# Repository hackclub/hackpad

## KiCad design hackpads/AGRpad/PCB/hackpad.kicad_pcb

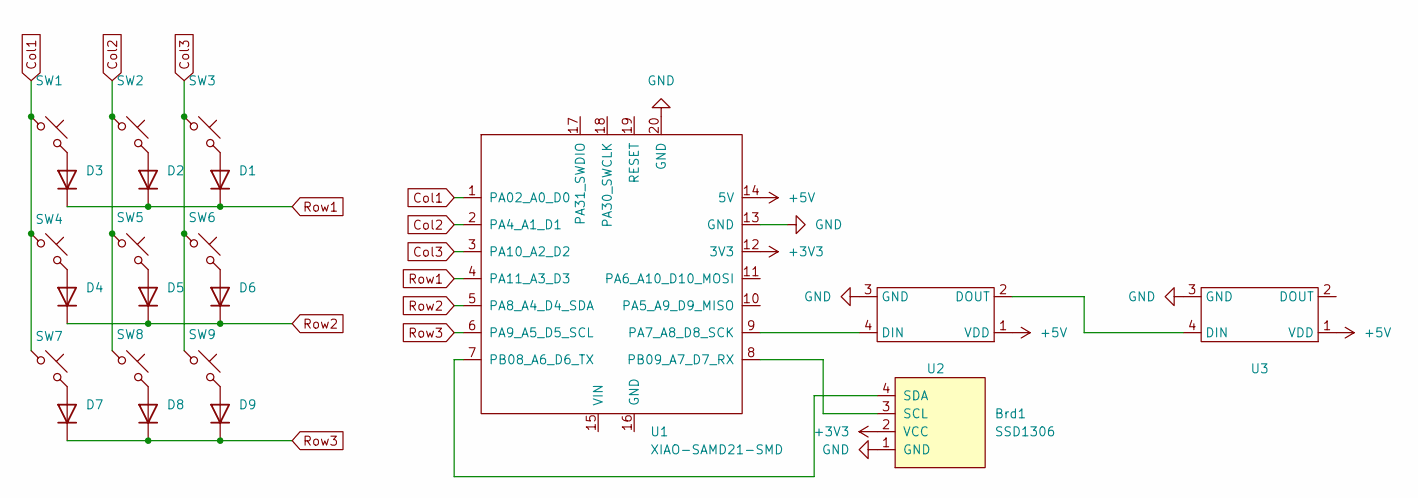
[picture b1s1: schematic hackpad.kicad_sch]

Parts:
Brd1: SSD1306; Display_128x64_096_I2C
D1, D2, D3, D4, D5, D6, D7, D8, D9: 1N4148WT; D_DO-34_SOD68_P7.62mm_Horizontal
SW1, SW2, SW3, SW4, SW5, SW6, SW7, SW8, SW9: SW_Push_45deg; SW_Cherry_MX_1.00u_PCB
U1: XIAO-SAMD21-SMD; XIAO-RP2040-DIP
U2, U3: LED_SK6812MINI_PLCC4_3.5x3.5mm_P1.75mm

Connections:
+3V3: Brd1.2 (VCC), U1.12 (3V3)
+5V: U1.14 (5V), U2.1 (VDD), U3.1 (VDD)
Col1: SW1.1, SW4.1, SW7.1, U1.1 (PA02_A0_D0)
Col2: SW2.1, SW5.1, SW8.1, U1.2 (PA4_A1_D1)
Col3: SW3.1, SW6.1, SW9.1, U1.3 (PA10_A2_D2)
GND: Brd1.1 (GND), U1.13 (GND), U1.20 (GND), U2.3 (GND), U3.3 (GND)
unnamed: Brd1.3 (SCL), U1.8 (PB09_A7_D7_RX)
unnamed: Brd1.4 (SDA), U1.7 (PB08_A6_D6_TX)
unnamed: D1.2 (A), SW3.2
unnamed: D2.2 (A), SW2.2
unnamed: D3.2 (A), SW1.2
unnamed: D4.2 (A), SW4.2
unnamed: D5.2 (A), SW5.2
unnamed: D6.2 (A), SW6.2
unnamed: D7.2 (A), SW7.2
unnamed: D8.2 (A), SW8.2
unnamed: D9.2 (A), SW9.2
unnamed: U1.9 (PA7_A8_D8_SCK), U2.4 (DIN)
unnamed: U2.2 (DOUT), U3.4 (DIN)
Row1: D1.1 (K), D2.1 (K), D3.1 (K), U1.4 (PA11_A3_D3)
Row2: D4.1 (K), D5.1 (K), D6.1 (K), U1.5 (PA8_A4_D4_SDA)
Row3: D7.1 (K), D8.1 (K), D9.1 (K), U1.6 (PA9_A5_D5_SCL)

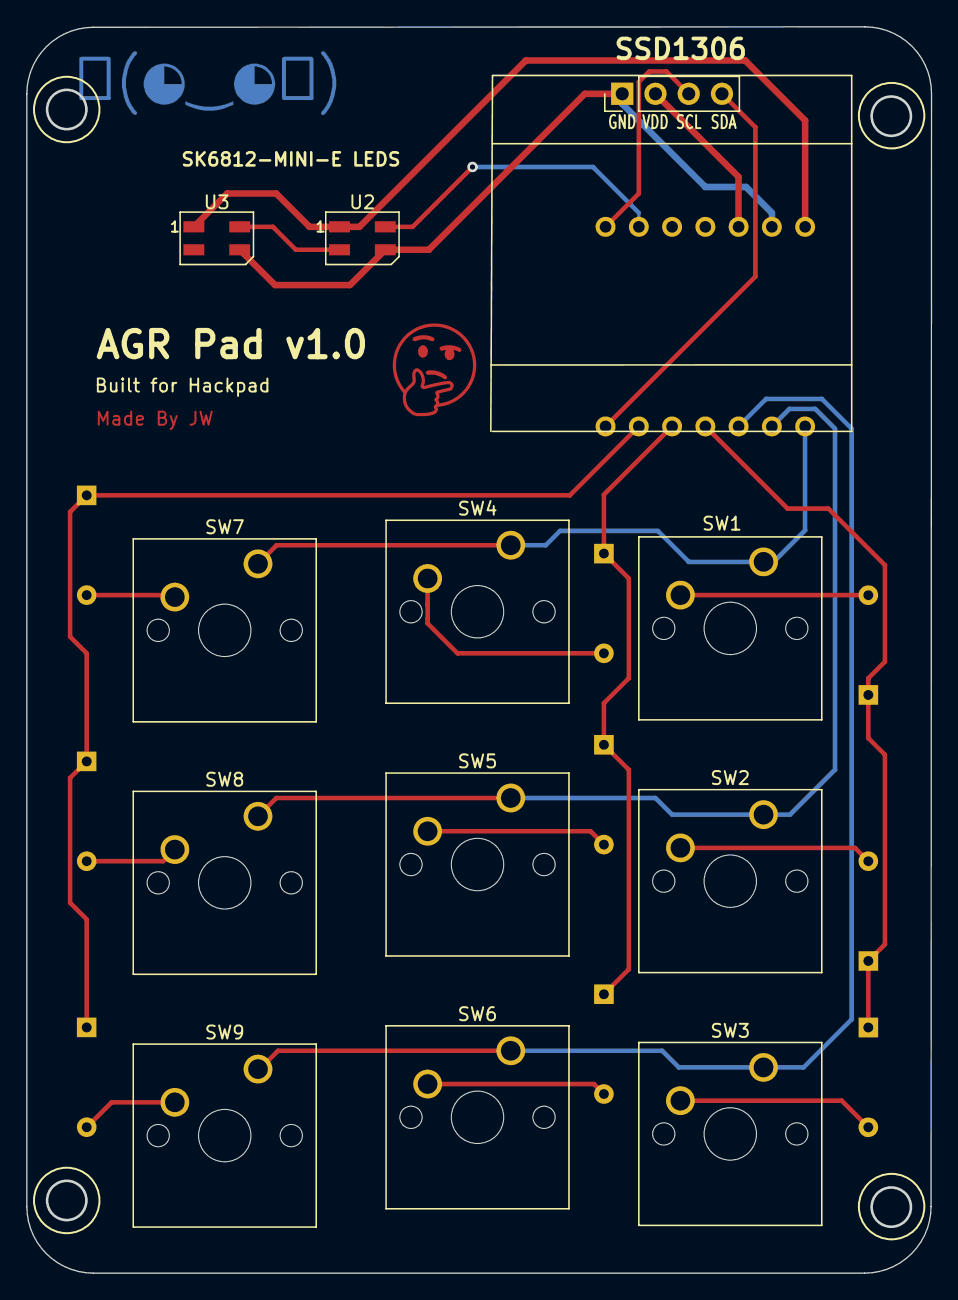
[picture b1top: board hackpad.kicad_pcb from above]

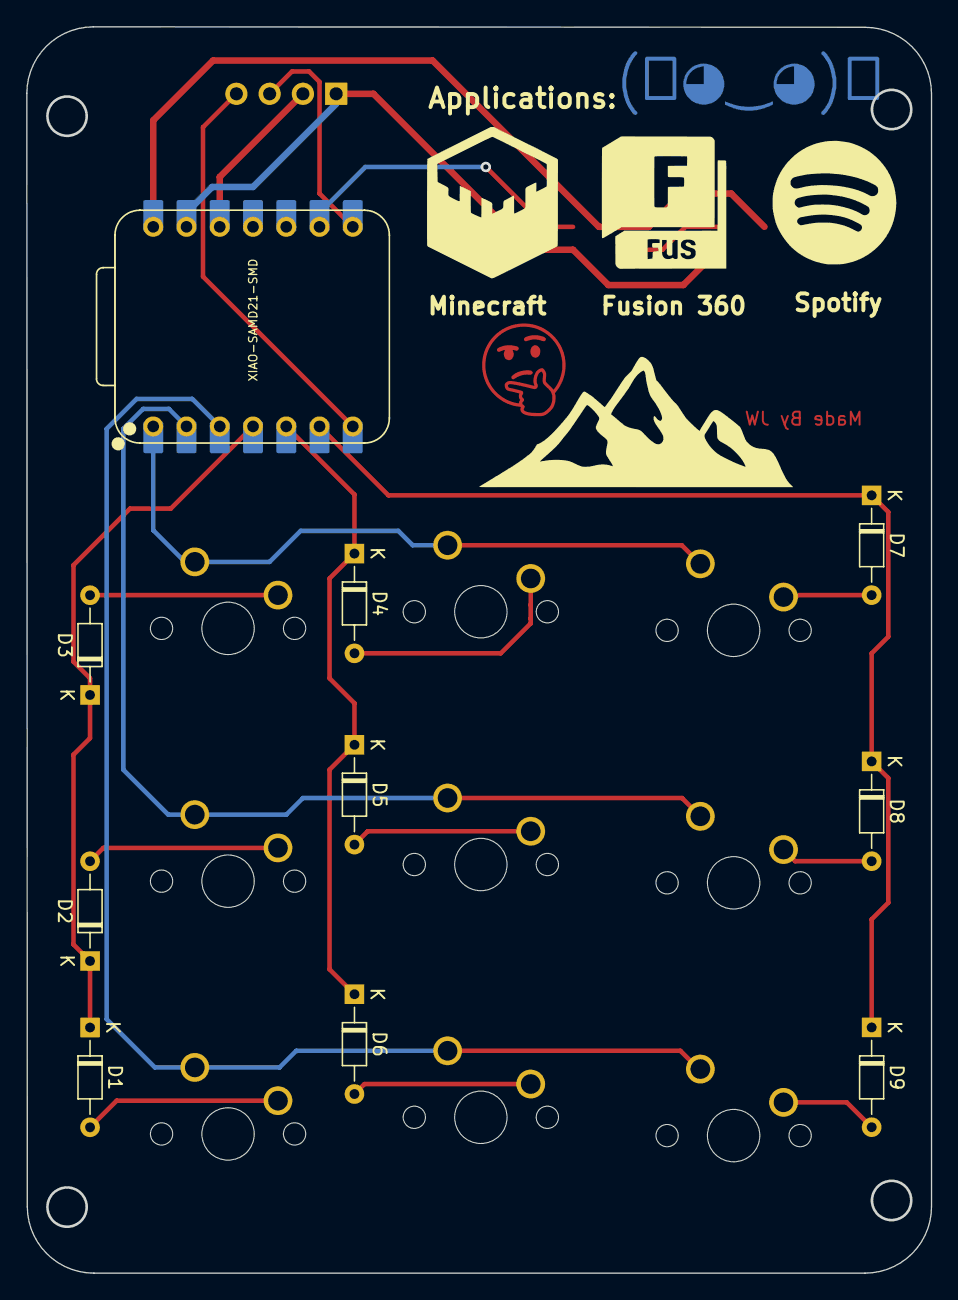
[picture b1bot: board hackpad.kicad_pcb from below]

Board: 2 copper layers, 69.1 x 95.2 mm, 22 parts (10 on the bottom side), 22 nets.

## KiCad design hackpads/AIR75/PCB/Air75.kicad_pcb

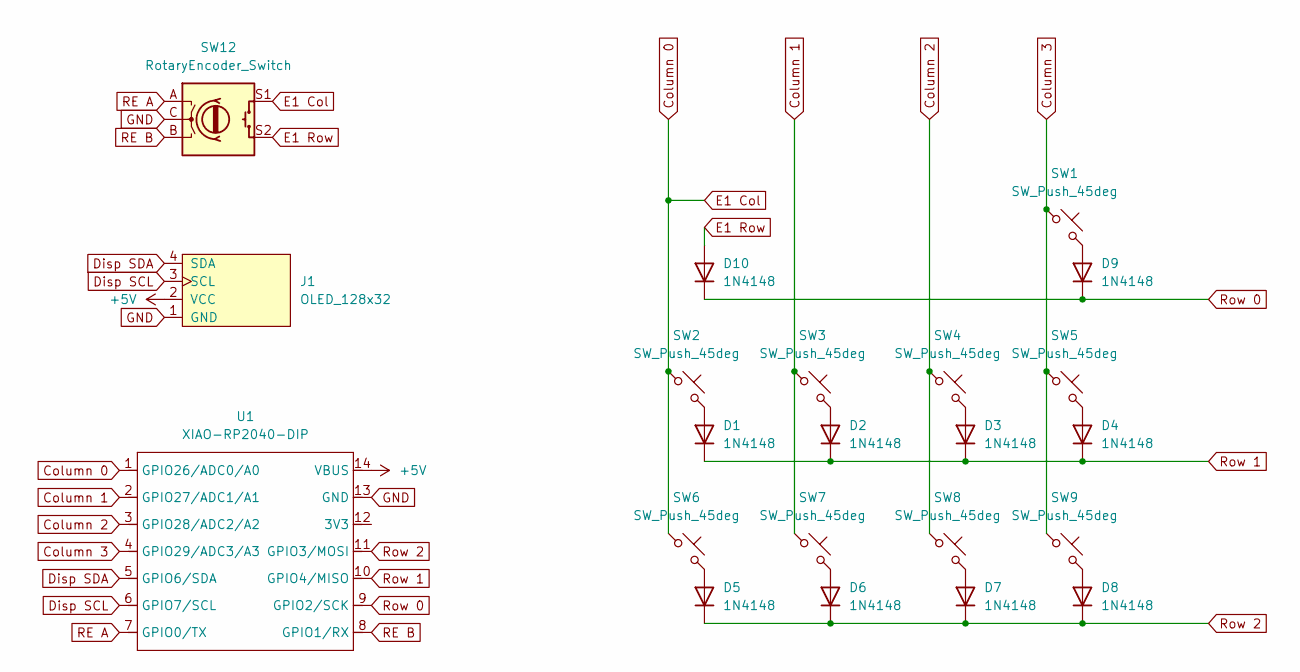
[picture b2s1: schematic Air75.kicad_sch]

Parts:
D1, D2, D3, D4, D5, D6, D7, D8, D9, D10: 1N4148; D_DO-35_SOD27_P7.62mm_Horizontal
J1: OLED_128x32
SW1, SW2, SW3, SW4, SW5, SW6, SW7, SW8, SW9: SW_Push_45deg; MX_PCB_1.00u
SW12: RotaryEncoder_Switch; Encoder_EC11_MX_Combo
U1: XIAO-RP2040-DIP

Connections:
+5V: J1.2 (VCC), U1.14 (VBUS)
Column 0: SW2.1, SW6.1, SW12.S1, U1.1 (GPIO26/ADC0/A0)
Column 1: SW3.1, SW7.1, U1.2 (GPIO27/ADC1/A1)
Column 2: SW4.1, SW8.1, U1.3 (GPIO28/ADC2/A2)
Column 3: SW1.1, SW5.1, SW9.1, U1.4 (GPIO29/ADC3/A3)
Disp SCL: J1.3 (SCL), U1.6 (GPIO7/SCL)
Disp SDA: J1.4 (SDA), U1.5 (GPIO6/SDA)
E1 Row: D10.2 (A), SW12.S2
GND: J1.1 (GND), SW12.C, U1.13 (GND)
unnamed: D1.2 (A), SW2.2
unnamed: D2.2 (A), SW3.2
unnamed: D3.2 (A), SW4.2
unnamed: D4.2 (A), SW5.2
unnamed: D5.2 (A), SW6.2
unnamed: D6.2 (A), SW7.2
unnamed: D7.2 (A), SW8.2
unnamed: D8.2 (A), SW9.2
unnamed: D9.2 (A), SW1.2
RE A: SW12.A, U1.7 (GPIO0/TX)
RE B: SW12.B, U1.8 (GPIO1/RX)
Row 0: D9.1 (K), D10.1 (K), U1.9 (GPIO2/SCK)
Row 1: D1.1 (K), D2.1 (K), D3.1 (K), D4.1 (K), U1.10 (GPIO4/MISO)
Row 2: D5.1 (K), D6.1 (K), D7.1 (K), D8.1 (K), U1.11 (GPIO3/MOSI)

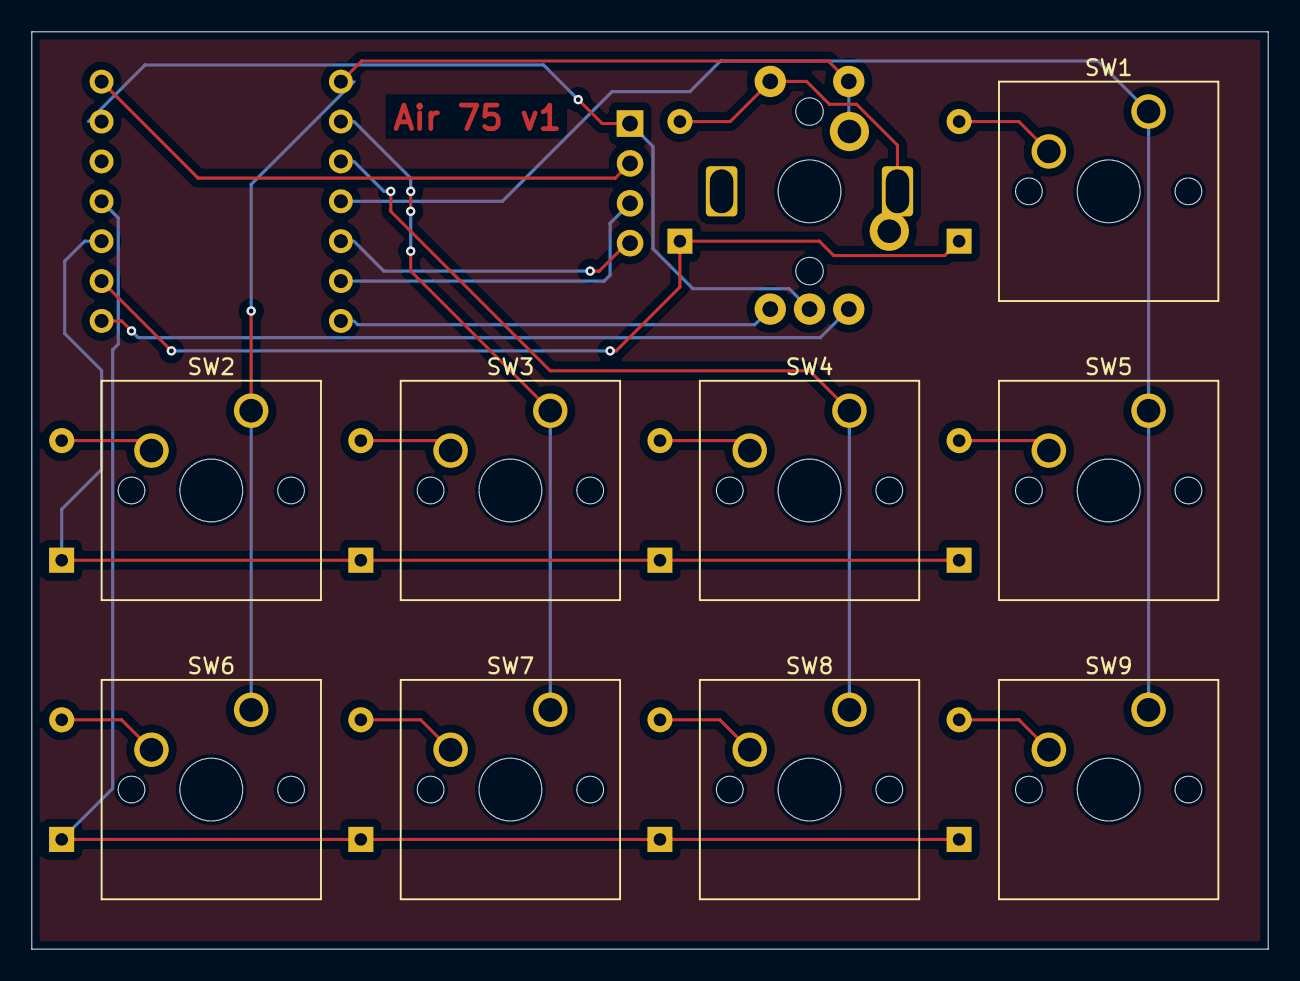
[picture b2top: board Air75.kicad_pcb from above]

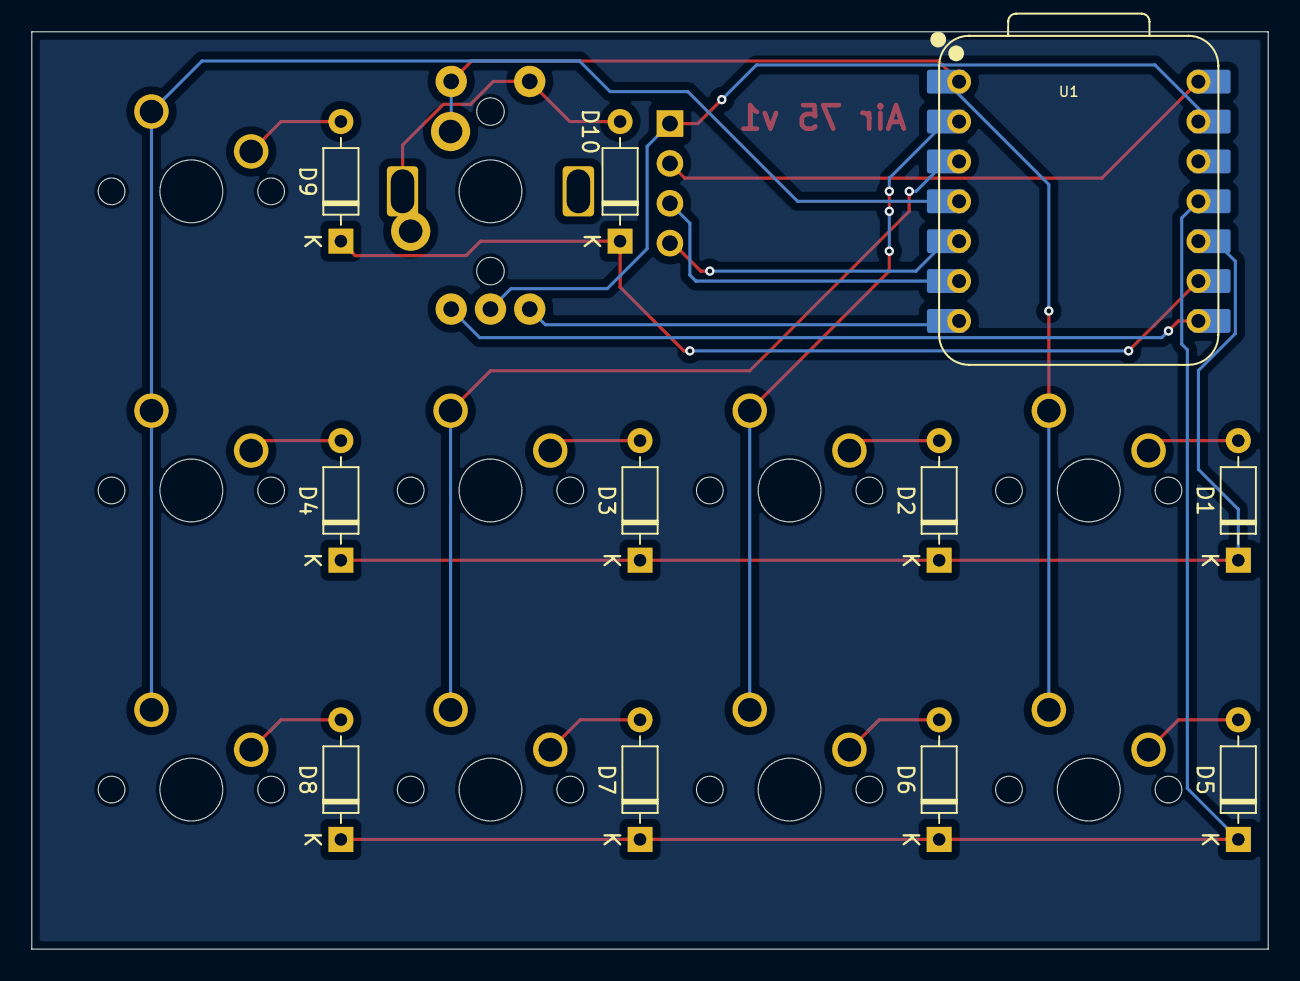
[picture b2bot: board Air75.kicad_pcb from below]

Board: 2 copper layers, 78.7 x 58.4 mm, 22 parts (11 on the bottom side), 23 nets.

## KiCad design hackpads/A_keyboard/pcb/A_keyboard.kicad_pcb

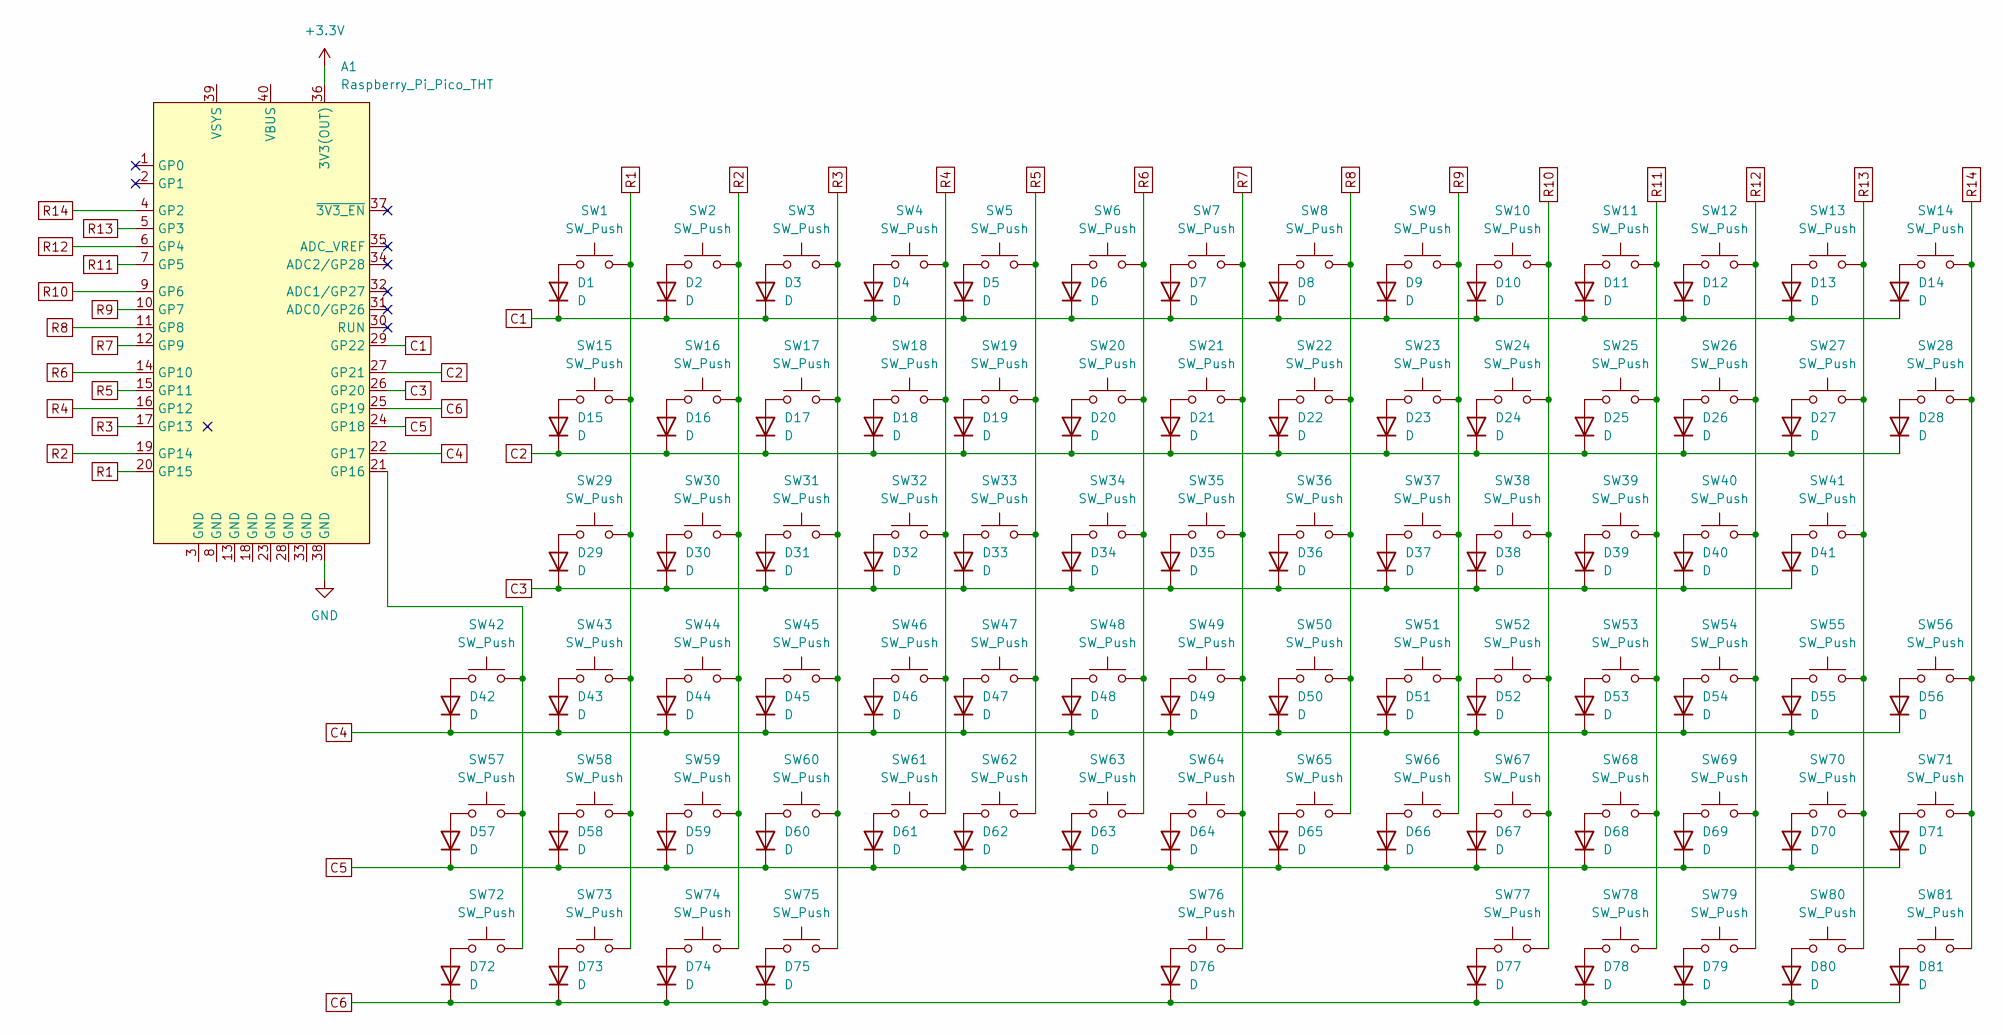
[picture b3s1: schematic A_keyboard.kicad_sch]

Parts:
A1: Raspberry_Pi_Pico_THT; RaspberryPi_Pico_Common_THT
D1, D2, D3, D4, D5, D6, D7, D8, D9, D10, D11, D12, D13, D14, D15, D16, D17, D18, D19, D20, D21, D22, D23, D24, D25, D26, D27, D28, D29, D30, D31, D32, D33, D34, D35, D36, D37, D38, D39, D40, D41, D42, D43, D44, D45, D46, D47, D48, D49, D50, D51, D52, D53, D54, D55, D56, D57, D58, D59, D60, D61, D62, D63, D64, D65, D66, D67, D68, D69, D70, D71, D72, D73, D74, D75, D76, D77, D78, D79, D80, D81: D; D_DO-35_SOD27_P7.62mm_Horizontal
SW1, SW2, SW3, SW4, SW5, SW6, SW7, SW8, SW9, SW10, SW11, SW12, SW13, SW14, SW15, SW16, SW17, SW18, SW19, SW20, SW21, SW22, SW23, SW24, SW25, SW26, SW27, SW30, SW31, SW32, SW33, SW34, SW35, SW36, SW37, SW38, SW39, SW40, SW41, SW42, SW44, SW45, SW46, SW47, SW48, SW49, SW50, SW51, SW52, SW53, SW54, SW55, SW56, SW57, SW59, SW60, SW61, SW62, SW63, SW64, SW65, SW66, SW67, SW68, SW69, SW70, SW71, SW72, SW77, SW78, SW79, SW80, SW81: SW_Push; MX-Hotswap-1U
SW28, SW58: SW_Push; MX-Hotswap-2U
SW29: SW_Push; MX-Hotswap-1.5U
SW43: SW_Push; MX-Hotswap-1.75U
SW73, SW74, SW75: SW_Push; MX-Hotswap-1.25U
SW76: SW_Push; MX-Hotswap-6.25U

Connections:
+3.3V: A1.36 (3V3(OUT))
C1: A1.29 (GP22), D1.1 (K), D2.1 (K), D3.1 (K), D4.1 (K), D5.1 (K), D6.1 (K), D7.1 (K), D8.1 (K), D9.1 (K), D10.1 (K), D11.1 (K), D12.1 (K), D13.1 (K), D14.1 (K)
C2: A1.27 (GP21), D15.1 (K), D16.1 (K), D17.1 (K), D18.1 (K), D19.1 (K), D20.1 (K), D21.1 (K), D22.1 (K), D23.1 (K), D24.1 (K), D25.1 (K), D26.1 (K), D27.1 (K), D28.1 (K)
C3: A1.26 (GP20), D29.1 (K), D30.1 (K), D31.1 (K), D32.1 (K), D33.1 (K), D34.1 (K), D35.1 (K), D36.1 (K), D37.1 (K), D38.1 (K), D39.1 (K), D40.1 (K), D41.1 (K)
C4: A1.22 (GP17), D42.1 (K), D43.1 (K), D44.1 (K), D45.1 (K), D46.1 (K), D47.1 (K), D48.1 (K), D49.1 (K), D50.1 (K), D51.1 (K), D52.1 (K), D53.1 (K), D54.1 (K), D55.1 (K), D56.1 (K)
C5: A1.24 (GP18), D57.1 (K), D58.1 (K), D59.1 (K), D60.1 (K), D61.1 (K), D62.1 (K), D63.1 (K), D64.1 (K), D65.1 (K), D66.1 (K), D67.1 (K), D68.1 (K), D69.1 (K), D70.1 (K), D71.1 (K)
C6: A1.25 (GP19), D72.1 (K), D73.1 (K), D74.1 (K), D75.1 (K), D76.1 (K), D77.1 (K), D78.1 (K), D79.1 (K), D80.1 (K), D81.1 (K)
GND: A1.38 (GND)
unnamed: A1.21 (GP16), SW42.1, SW57.1, SW72.1
unnamed: D1.2 (A), SW1.2
unnamed: D2.2 (A), SW2.2
unnamed: D3.2 (A), SW3.2
unnamed: D4.2 (A), SW4.2
unnamed: D5.2 (A), SW5.2
unnamed: D6.2 (A), SW6.2
unnamed: D7.2 (A), SW7.2
unnamed: D8.2 (A), SW8.2
unnamed: D9.2 (A), SW9.2
unnamed: D10.2 (A), SW10.2
unnamed: D11.2 (A), SW11.2
unnamed: D12.2 (A), SW12.2
unnamed: D13.2 (A), SW13.2
unnamed: D14.2 (A), SW14.2
unnamed: D15.2 (A), SW15.2
unnamed: D16.2 (A), SW16.2
unnamed: D17.2 (A), SW17.2
unnamed: D18.2 (A), SW18.2
unnamed: D19.2 (A), SW19.2
unnamed: D20.2 (A), SW20.2
unnamed: D21.2 (A), SW21.2
unnamed: D22.2 (A), SW22.2
unnamed: D23.2 (A), SW23.2
unnamed: D24.2 (A), SW24.2
unnamed: D25.2 (A), SW25.2
unnamed: D26.2 (A), SW26.2
unnamed: D27.2 (A), SW27.2
unnamed: D28.2 (A), SW28.2
unnamed: D29.2 (A), SW29.2
unnamed: D30.2 (A), SW30.2
unnamed: D31.2 (A), SW31.2
unnamed: D32.2 (A), SW32.2
unnamed: D33.2 (A), SW33.2
unnamed: D34.2 (A), SW34.2
unnamed: D35.2 (A), SW35.2
unnamed: D36.2 (A), SW36.2
unnamed: D37.2 (A), SW37.2
unnamed: D38.2 (A), SW38.2
unnamed: D39.2 (A), SW39.2
unnamed: D40.2 (A), SW40.2
unnamed: D41.2 (A), SW41.2
unnamed: D42.2 (A), SW42.2
unnamed: D43.2 (A), SW43.2
unnamed: D44.2 (A), SW44.2
unnamed: D45.2 (A), SW45.2
unnamed: D46.2 (A), SW46.2
unnamed: D47.2 (A), SW47.2
unnamed: D48.2 (A), SW48.2
unnamed: D49.2 (A), SW49.2
unnamed: D50.2 (A), SW50.2
unnamed: D51.2 (A), SW51.2
unnamed: D52.2 (A), SW52.2
unnamed: D53.2 (A), SW53.2
unnamed: D54.2 (A), SW54.2
unnamed: D55.2 (A), SW55.2
unnamed: D56.2 (A), SW56.2
unnamed: D57.2 (A), SW57.2
unnamed: D58.2 (A), SW58.2
unnamed: D59.2 (A), SW59.2
unnamed: D60.2 (A), SW60.2
unnamed: D61.2 (A), SW61.2
unnamed: D62.2 (A), SW62.2
unnamed: D63.2 (A), SW63.2
unnamed: D64.2 (A), SW64.2
unnamed: D65.2 (A), SW65.2
unnamed: D66.2 (A), SW66.2
unnamed: D67.2 (A), SW67.2
unnamed: D68.2 (A), SW68.2
unnamed: D69.2 (A), SW69.2
unnamed: D70.2 (A), SW70.2
unnamed: D71.2 (A), SW71.2
unnamed: D72.2 (A), SW72.2
unnamed: D73.2 (A), SW73.2
unnamed: D74.2 (A), SW74.2
unnamed: D75.2 (A), SW75.2
unnamed: D76.2 (A), SW76.2
unnamed: D77.2 (A), SW77.2
unnamed: D78.2 (A), SW78.2
unnamed: D79.2 (A), SW79.2
unnamed: D80.2 (A), SW80.2
unnamed: D81.2 (A), SW81.2
R1: A1.20 (GP15), SW1.1, SW15.1, SW29.1, SW43.1, SW58.1, SW73.1
R2: A1.19 (GP14), SW2.1, SW16.1, SW30.1, SW44.1, SW59.1, SW74.1
R3: A1.17 (GP13), SW3.1, SW17.1, SW31.1, SW45.1, SW60.1, SW75.1
R4: A1.16 (GP12), SW4.1, SW18.1, SW32.1, SW46.1, SW61.1
R5: A1.15 (GP11), SW5.1, SW19.1, SW33.1, SW47.1, SW62.1
R6: A1.14 (GP10), SW6.1, SW20.1, SW34.1, SW48.1, SW63.1
R7: A1.12 (GP9), SW7.1, SW21.1, SW35.1, SW49.1, SW64.1, SW76.1
R8: A1.11 (GP8), SW8.1, SW22.1, SW36.1, SW50.1, SW65.1
R9: A1.10 (GP7), SW9.1, SW23.1, SW37.1, SW51.1, SW66.1
R10: A1.9 (GP6), SW10.1, SW24.1, SW38.1, SW52.1, SW67.1, SW77.1
R11: A1.7 (GP5), SW11.1, SW25.1, SW39.1, SW53.1, SW68.1, SW78.1
R12: A1.6 (GP4), SW12.1, SW26.1, SW40.1, SW54.1, SW69.1, SW79.1
R13: A1.5 (GP3), SW13.1, SW27.1, SW41.1, SW55.1, SW70.1, SW80.1
R14: A1.4 (GP2), SW14.1, SW28.1, SW56.1, SW71.1, SW81.1

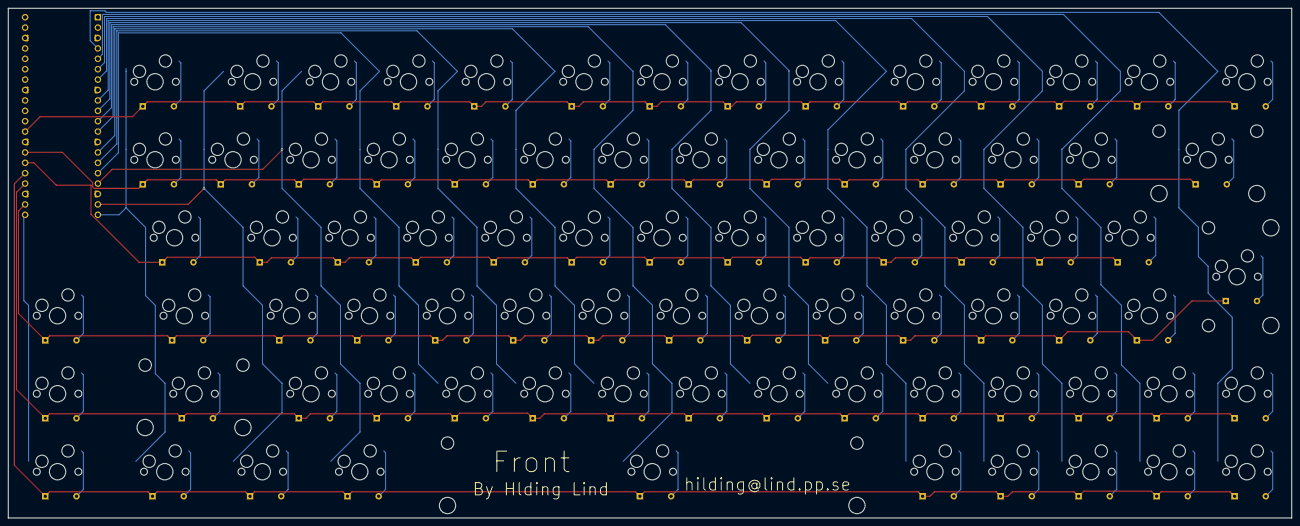
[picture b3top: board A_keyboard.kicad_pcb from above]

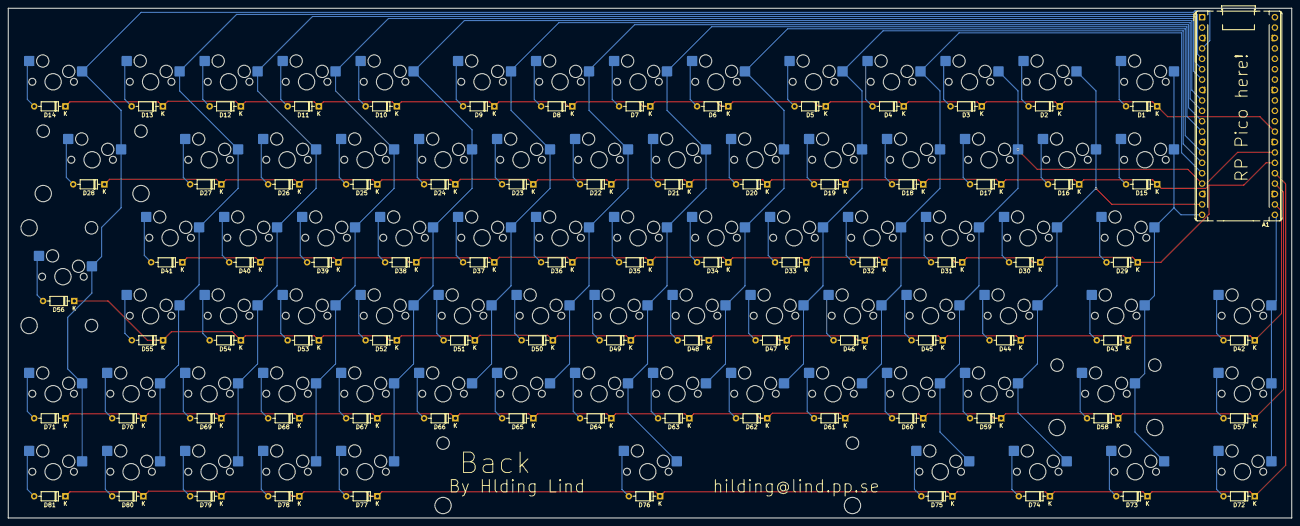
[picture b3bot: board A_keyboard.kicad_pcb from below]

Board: 2 copper layers, 313.5 x 124.5 mm, 163 parts (163 on the bottom side), 102 nets.

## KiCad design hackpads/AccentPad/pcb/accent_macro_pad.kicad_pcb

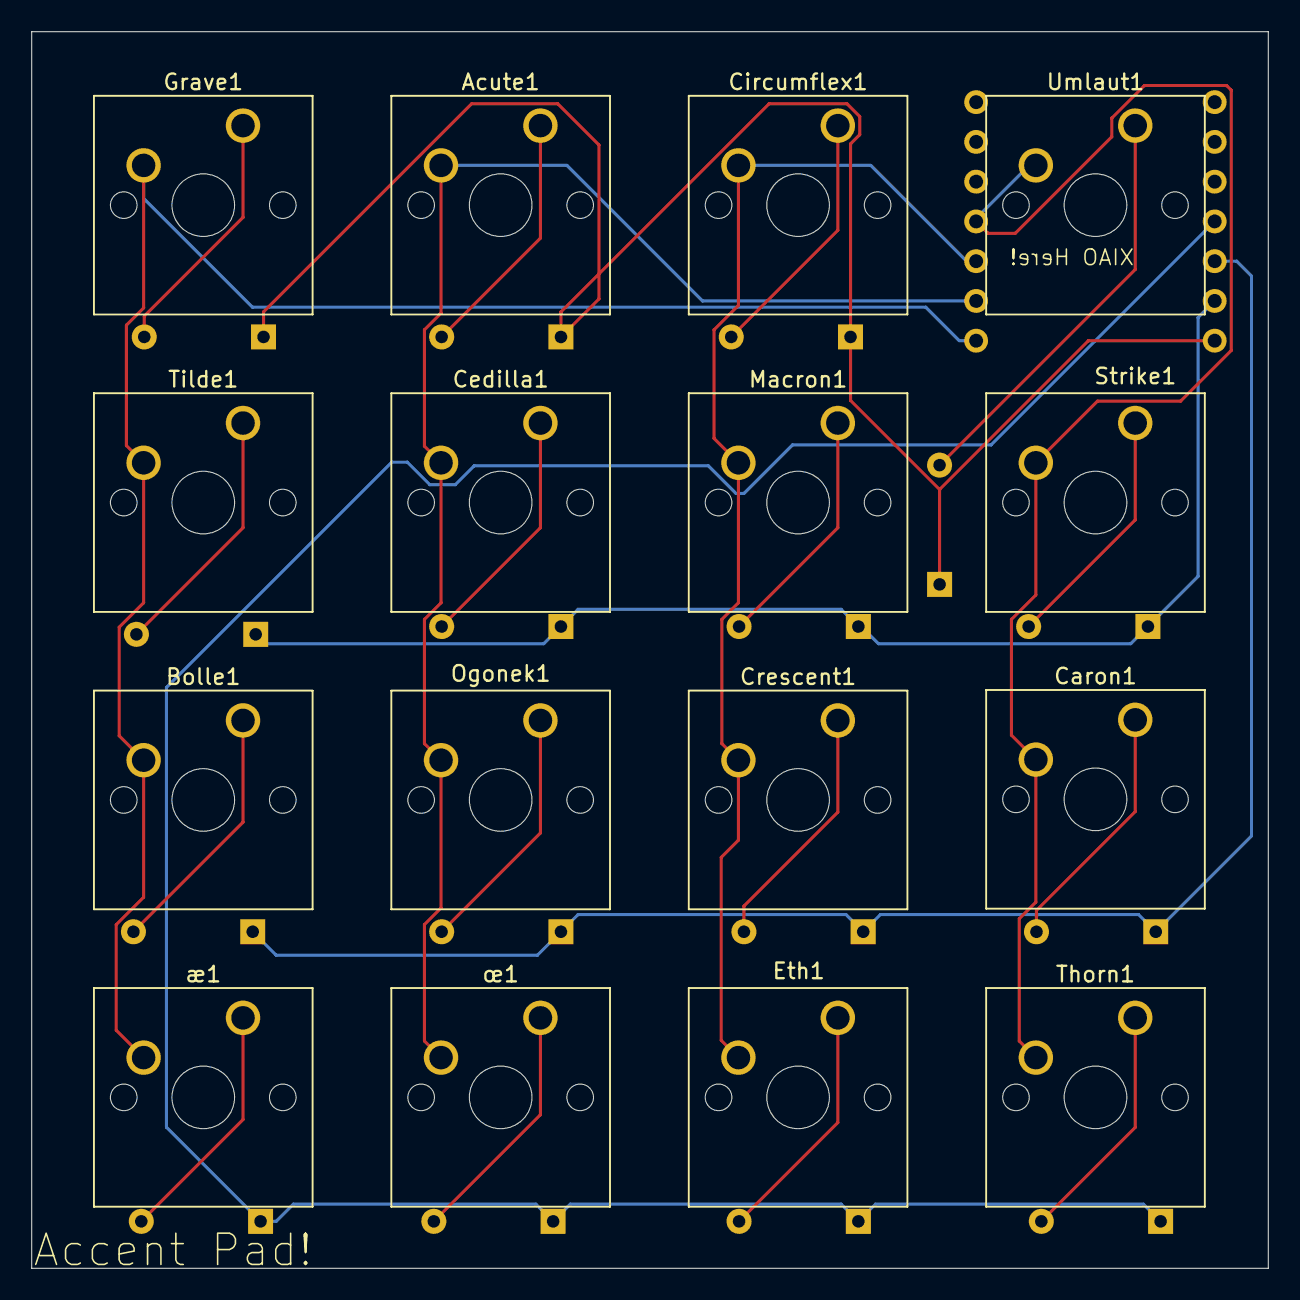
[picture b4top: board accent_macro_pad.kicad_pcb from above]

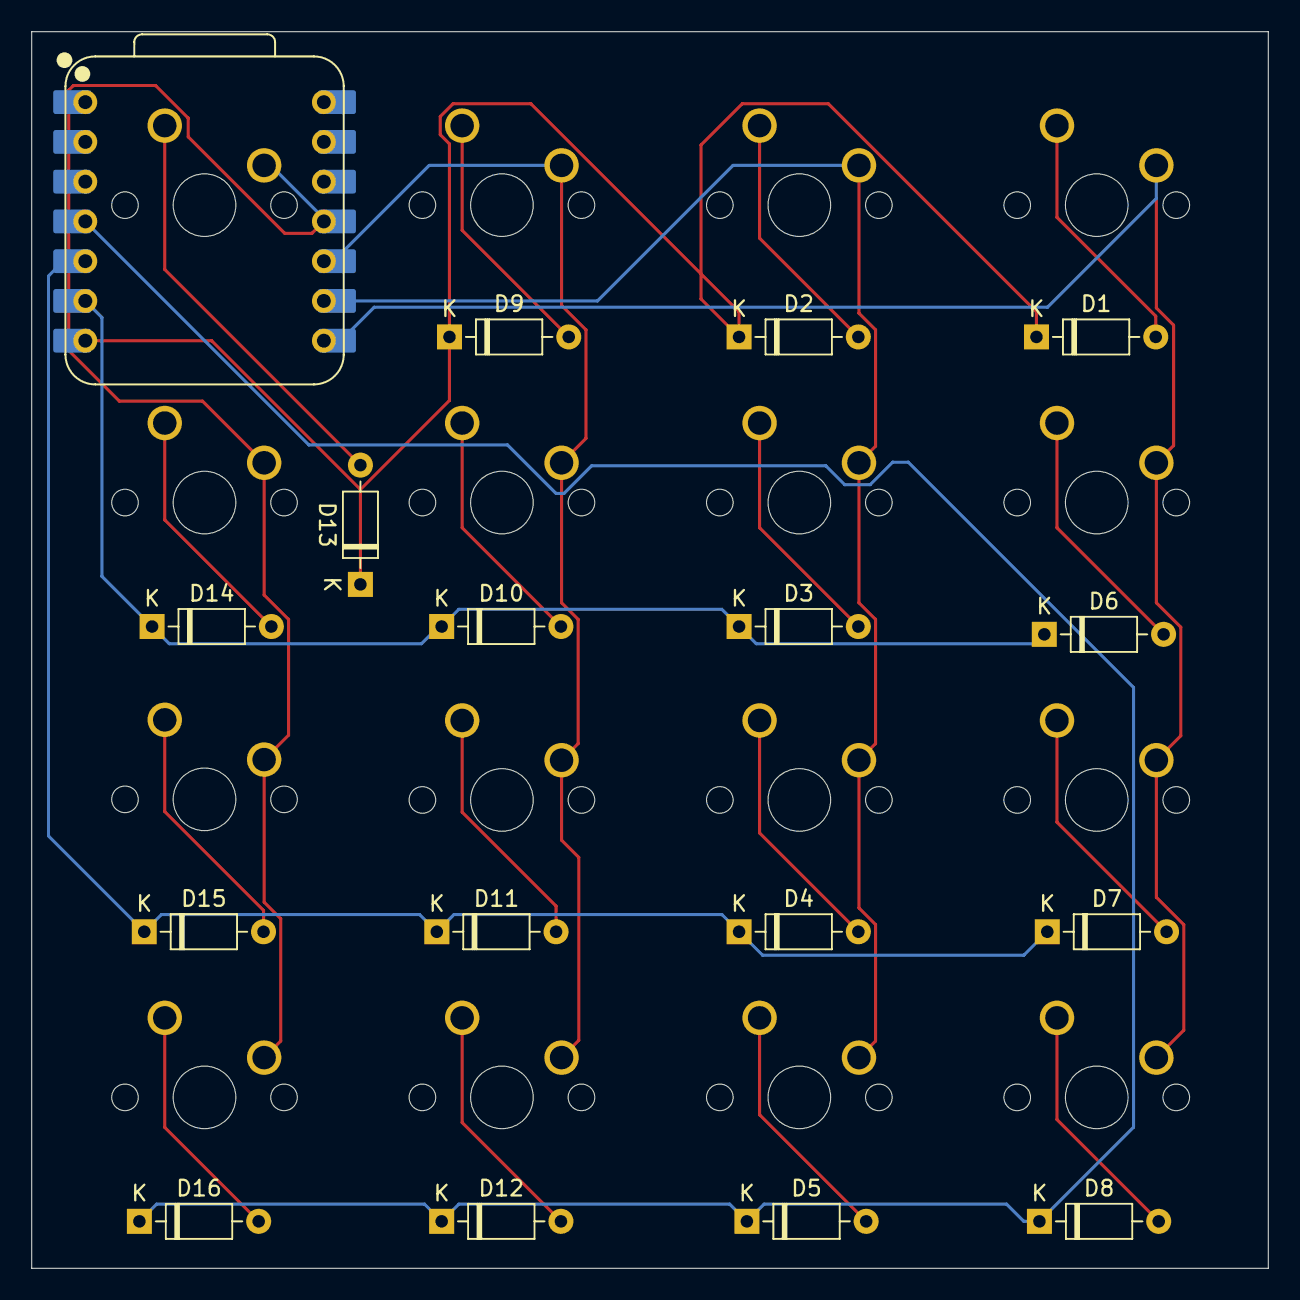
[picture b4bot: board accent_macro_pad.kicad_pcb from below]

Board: 2 copper layers, 79.0 x 79.0 mm, 33 parts (17 on the bottom side), 24 nets.

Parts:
Acute1: SW_Push; SW_Cherry_MX_1.00u_PCB
Bolle1: SW_Push; SW_Cherry_MX_1.00u_PCB
Caron1: SW_Push; SW_Cherry_MX_1.00u_PCB
Cedilla1: SW_Push; SW_Cherry_MX_1.00u_PCB
Circumflex1: SW_Push; SW_Cherry_MX_1.00u_PCB
Crescent1: SW_Push; SW_Cherry_MX_1.00u_PCB
D1, D2, D3, D4, D5, D6, D7, D8, D9, D10, D11, D12, D13, D14, D15, D16: 1N4148; D_DO-35_SOD27_P7.62mm_Horizontal
Eth1: SW_Push; SW_Cherry_MX_1.00u_PCB
Grave1: SW_Push; SW_Cherry_MX_1.00u_PCB
Macron1: SW_Push; SW_Cherry_MX_1.00u_PCB
Ogonek1: SW_Push; SW_Cherry_MX_1.00u_PCB
Strike1: SW_Push; SW_Cherry_MX_1.00u_PCB
Thorn1: SW_Push; SW_Cherry_MX_1.00u_PCB
Tilde1: SW_Push; SW_Cherry_MX_1.00u_PCB
U1: XIAO-RP2040-SMD; XIAO-RP2040-DIP
Umlaut1: SW_Push; SW_Cherry_MX_1.00u_PCB
æ1: SW_Push; SW_Cherry_MX_1.00u_PCB
œ1: SW_Push; SW_Cherry_MX_1.00u_PCB

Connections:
unnamed: D1.2 (A), Grave1.1
unnamed: D1.1 (K), D2.1 (K), D9.1 (K), D13.1 (K), U1.7 (GPIO0_D6_TX)
unnamed: Acute1.1, D2.2 (A)
unnamed: Cedilla1.1, D3.2 (A)
unnamed: D4.2 (A), Ogonek1.1
unnamed: D5.2 (A), œ1.1
unnamed: D6.2 (A), Tilde1.1
unnamed: Bolle1.1, D7.2 (A)
unnamed: D8.2 (A), æ1.1
unnamed: Circumflex1.1, D9.2 (A)
unnamed: D10.2 (A), Macron1.1
unnamed: D3.1 (K), D6.1 (K), D10.1 (K), D14.1 (K), U1.6 (GPIO7_D5_SCL)
unnamed: Crescent1.1, D11.2 (A)
unnamed: D4.1 (K), D7.1 (K), D11.1 (K), D15.1 (K), U1.5 (GPIO6_D4_SDA)
unnamed: D12.2 (A), Eth1.1
unnamed: D5.1 (K), D8.1 (K), D12.1 (K), D16.1 (K), U1.4 (GPIO29_A3_D3)
unnamed: D13.2 (A), Umlaut1.1
unnamed: D14.2 (A), Strike1.1
unnamed: Caron1.1, D15.2 (A)
unnamed: D16.2 (A), Thorn1.1
unnamed: Bolle1.2, Grave1.2, Tilde1.2, U1.8 (GPIO1_D7_CSn_RX), æ1.2
unnamed: Acute1.2, Cedilla1.2, Ogonek1.2, U1.9 (GPIO2_D8_SCK), œ1.2
unnamed: Caron1.2, Strike1.2, Thorn1.2, U1.11 (GPIO3_D10_MOSI), Umlaut1.2
unnamed: Circumflex1.2, Crescent1.2, Eth1.2, Macron1.2, U1.10 (GPIO4_D9_MISO)

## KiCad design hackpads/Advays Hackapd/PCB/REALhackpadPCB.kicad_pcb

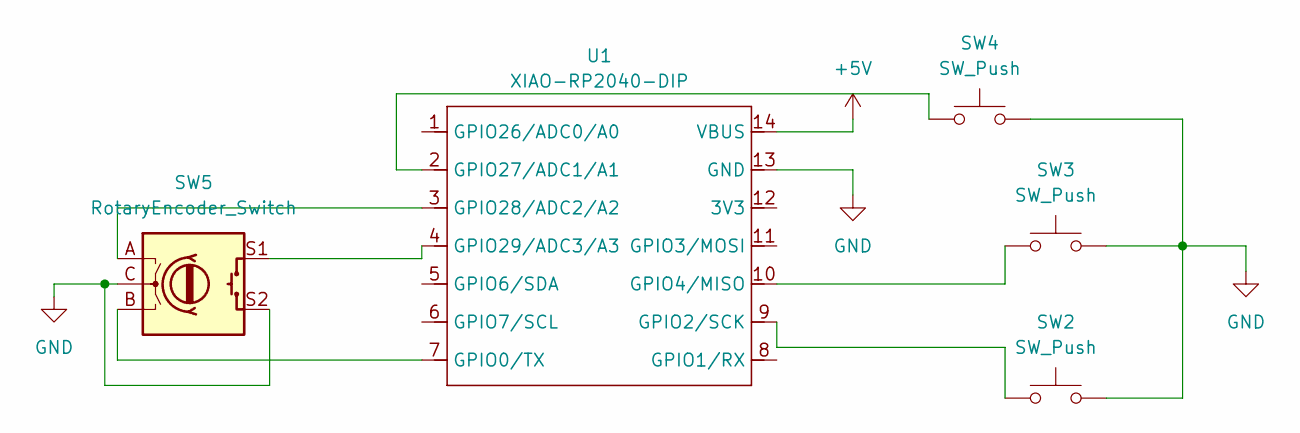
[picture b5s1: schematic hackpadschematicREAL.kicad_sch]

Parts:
SW2, SW3, SW4: SW_Push; SW_Cherry_MX_1.00u_PCB
SW5: RotaryEncoder_Switch; RotaryEncoder_Alps_EC11E-Switch_Vertical_H20mm_CircularMoun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
U1: XIAO-RP2040-DIP

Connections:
+5V: U1.14 (VBUS)
GND: SW2.2, SW3.2, SW4.2, SW5.C, SW5.S2, U1.13 (GND)
unnamed: SW5.B, U1.7 (GPIO0/TX)
unnamed: SW2.1, U1.9 (GPIO2/SCK)
unnamed: SW3.1, U1.10 (GPIO4/MISO)
unnamed: SW4.1, U1.2 (GPIO27/ADC1/A1)
unnamed: SW5.A, U1.3 (GPIO28/ADC2/A2)
unnamed: SW5.S1, U1.4 (GPIO29/ADC3/A3)

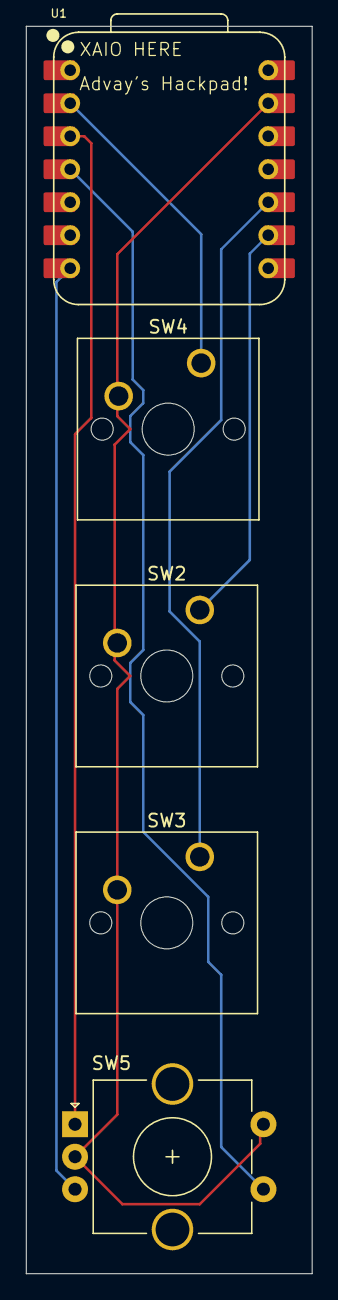
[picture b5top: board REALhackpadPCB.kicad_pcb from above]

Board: 2 copper layers, 22.0 x 96.0 mm, 5 parts (0 on the bottom side), 7 nets.

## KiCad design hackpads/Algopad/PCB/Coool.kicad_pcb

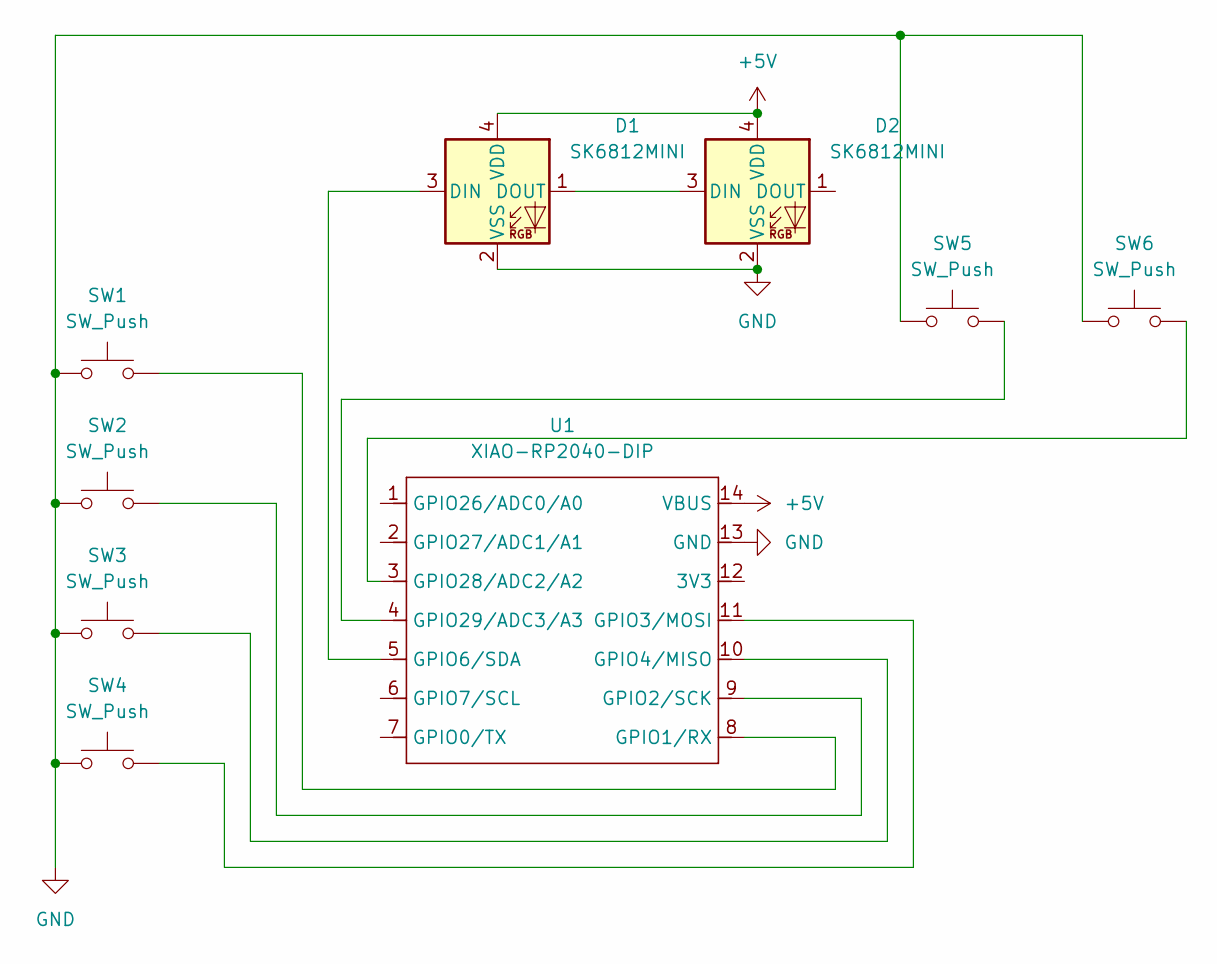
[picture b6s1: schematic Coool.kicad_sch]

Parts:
D1, D2: SK6812MINI; LED_SK6812MINI_PLCC4_3.5x3.5mm_P1.75mm
SW1, SW2, SW3, SW4, SW5, SW6: SW_Push; SW_Cherry_MX_1.00u_PCB
U1: XIAO-RP2040-DIP

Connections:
+5V: D1.4 (VDD), D2.4 (VDD), U1.14 (VBUS)
GND: D1.2 (VSS), D2.2 (VSS), SW1.1, SW2.1, SW3.1, SW4.1, SW5.1, SW6.1, U1.13 (GND)
unnamed: D1.3 (DIN), U1.5 (GPIO6/SDA)
unnamed: D1.1 (DOUT), D2.3 (DIN)
unnamed: SW1.2, U1.8 (GPIO1/RX)
unnamed: SW2.2, U1.9 (GPIO2/SCK)
unnamed: SW4.2, U1.11 (GPIO3/MOSI)
unnamed: SW3.2, U1.10 (GPIO4/MISO)
unnamed: SW6.2, U1.3 (GPIO28/ADC2/A2)
unnamed: SW5.2, U1.4 (GPIO29/ADC3/A3)
